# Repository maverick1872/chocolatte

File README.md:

# chocolatte
Custom split columnar (column staggered) keyboard heavily influenced on the crkbd, corne-ish zen, chocolad, and others

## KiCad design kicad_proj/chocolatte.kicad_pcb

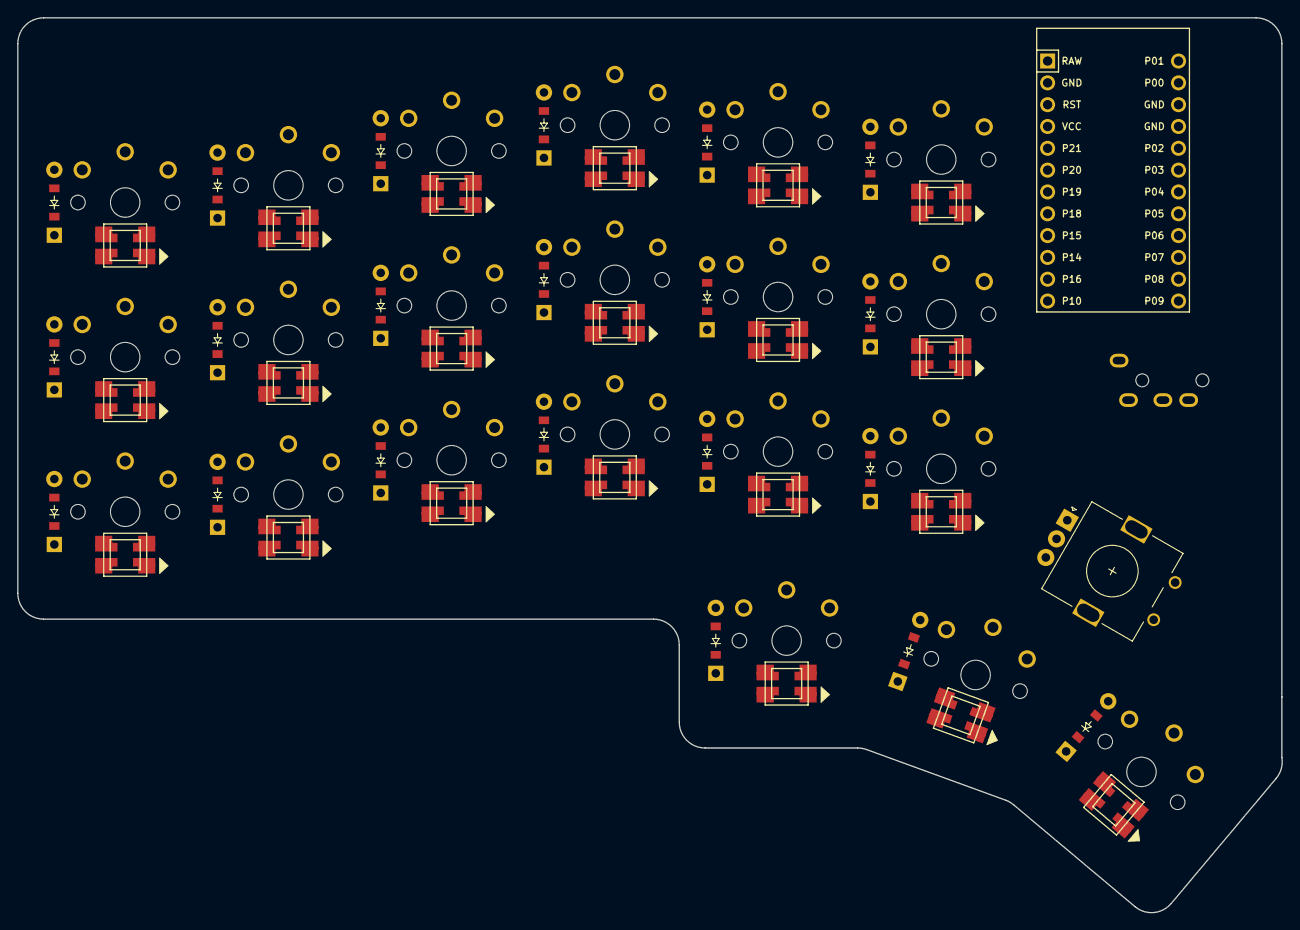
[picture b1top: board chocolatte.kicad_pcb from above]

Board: 2 copper layers, 147.2 x 104.2 mm, 65 parts (0 on the bottom side), 25 nets, no tracks yet.

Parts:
D1, D2, D3, D4, D5, D6, D7, D8, D9, D10, D11, D12, D13, D14, D15, D16, D17, D18, D19, D20, D21: ComboDiode
LED1, LED2, LED3, LED4, LED5, LED6, LED7, LED8, LED9, LED10, LED11, LED12, LED13, LED14, LED15, LED16, LED17, LED18, LED19, LED20, LED21: WS2812B
MCU1: ProMicro
ROT1: rotary_encoder
S1, S2, S3, S4, S5, S6, S7, S8, S9, S10, S11, S12, S13, S14, S15, S16, S17, S18, S19, S20, S21: PG1350

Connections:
GND: LED1.3, LED1.33, LED2.3, LED2.33, LED3.3, LED3.33, LED4.3, LED4.33, LED5.3, LED5.33, LED6.3, LED6.33, LED7.3, LED7.33, LED8.3, LED8.33, LED9.3, LED9.33, LED10.3, LED10.33, LED11.3, LED11.33, LED12.3, LED12.33, LED13.3, LED13.33, LED14.3, LED14.33, LED15.3, LED15.33, LED16.3, LED16.33, LED17.3, LED17.33, LED18.3, LED18.33, LED19.3, LED19.33, LED20.3, LED20.33, LED21.3, LED21.33, MCU1.2, MCU1.15, MCU1.16, ROT1.B, S1.2, S2.2, S3.2, S4.2, S5.2, S6.2, S7.2, S8.2, S9.2, S10.2, S11.2, S12.2, S13.2, S14.2, S15.2, S16.2, S17.2, S18.2, S19.2, S20.2, S21.2
VCC: LED1.1, LED1.11, LED2.1, LED2.11, LED3.1, LED3.11, LED4.1, LED4.11, LED5.1, LED5.11, LED6.1, LED6.11, LED7.1, LED7.11, LED8.1, LED8.11, LED9.1, LED9.11, LED10.1, LED10.11, LED11.1, LED11.11, LED12.1, LED12.11, LED13.1, LED13.11, LED14.1, LED14.11, LED15.1, LED15.11, LED16.1, LED16.11, LED17.1, LED17.11, LED18.1, LED18.11, LED19.1, LED19.11, LED20.1, LED20.11, LED21.1, LED21.11, MCU1.4
matrix_index_bottom: D13.1, D13.2, S13.1
matrix_index_home: D14.1, D14.2, MCU1.10, S14.1
matrix_index_top: D15.1, D15.2, MCU1.9, S15.1
matrix_inner_bottom: D16.1, D16.2, MCU1.11, S16.1
matrix_inner_home: D17.1, D17.2, S17.1
matrix_inner_top: D18.1, D18.2, MCU1.8, S18.1
matrix_middle_bottom: D10.1, D10.2, MCU1.12, S10.1
matrix_middle_home: D11.1, D11.2, S11.1
matrix_middle_top: D12.1, D12.2, S12.1
matrix_outer_bottom: D1.1, D1.2, MCU1.13, S1.1
matrix_outer_home: D2.1, D2.2, MCU1.17, S2.1
matrix_outer_top: D3.1, D3.2, MCU1.18, S3.1
matrix_pinky_bottom: D4.1, D4.2, MCU1.19, S4.1
matrix_pinky_home: D5.1, D5.2, MCU1.20, S5.1
matrix_pinky_top: D6.1, D6.2, MCU1.21, S6.1
matrix_ring_bottom: D7.1, D7.2, MCU1.22, S7.1
matrix_ring_home: D8.1, D8.2, MCU1.23, S8.1
matrix_ring_top: D9.1, D9.2, MCU1.24, S9.1
thumbfan_far_thumb: D21.1, D21.2, S21.1
thumbfan_home_thumb: D20.1, D20.2, S20.1
thumbfan_near_thumb: D19.1, D19.2, S19.1
undefined: ROT1.1, ROT1.2, ROT1.A, ROT1.C
unknown: D1.1, D1.2, D2.1, D2.2, D3.1, D3.2, D4.1, D4.2, D5.1, D5.2, D6.1, D6.2, D7.1, D7.2, D8.1, D8.2, D9.1, D9.2, D10.1, D10.2, D11.1, D11.2, D12.1, D12.2, D13.1, D13.2, D14.1, D14.2, D15.1, D15.2, D16.1, D16.2, D17.1, D17.2, D18.1, D18.2, D19.1, D19.2, D20.1, D20.2, D21.1, D21.2, LED1.2, LED1.4, LED1.22, LED1.44, LED2.2, LED2.4, LED2.22, LED2.44, LED3.2, LED3.4, LED3.22, LED3.44, LED4.2, LED4.4, LED4.22, LED4.44, LED5.2, LED5.4, LED5.22, LED5.44, LED6.2, LED6.4, LED6.22, LED6.44, LED7.2, LED7.4, LED7.22, LED7.44, LED8.2, LED8.4, LED8.22, LED8.44, LED9.2, LED9.4, LED9.22, LED9.44, LED10.2, LED10.4, LED10.22, LED10.44, LED11.2, LED11.4, LED11.22, LED11.44, LED12.2, LED12.4, LED12.22, LED12.44, LED13.2, LED13.4, LED13.22, LED13.44, LED14.2, LED14.4, LED14.22, LED14.44, LED15.2, LED15.4, LED15.22, LED15.44, LED16.2, LED16.4, LED16.22, LED16.44, LED17.2, LED17.4, LED17.22, LED17.44, LED18.2, LED18.4, LED18.22, LED18.44, LED19.2, LED19.4, LED19.22, LED19.44, LED20.2, LED20.4, LED20.22, LED20.44, LED21.2, LED21.4, LED21.22, LED21.44

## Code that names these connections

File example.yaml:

points:
  key:
    padding: cy
    footprints:
      choc:
        type: choc
        nets:
          from: =name
          to: GND
        params:
          keycaps: true
          reverse: true
      diode:
        type: diode
        params:
          tracks: true
        nets:
          from: =name
          to: unknown
        anchor:
          shift: [0, -5]

  zones:
    matrix:
      columns:
        outer:
        pinky:
          stagger: 2
        ring:
          stagger: 4
        middle:
          stagger: 3
        index:
          stagger: -2
        inner:
          stagger: -2
      rows:
        bottom:
        home:
        top:
    thumbfan:
      anchor:
        ref: matrix_inner_bottom
        shift: [-25, -20]
      columns:
        near:
        home:
          spread: cx+4
          stagger: -4
          rotate: -20
        far:
          spread: cx+4
          stagger: -4
          rotate: -20
      rows:
        thumb:

outlines:
  exports:
    keys:
      - type: keys
        side: left
        size: 18
    plate:
      - type: keys
        side: left
        size: 25
        corner: 4
    promicro_mounts:
      - type: rectangle
        anchor:
          - ref: matrix_middle_top
            shift: [0, (cy/2) + 4 ]
            rotate: 270
        size: [82,70]
        corner: 4
    merged:
      - type: outline # keys
        name: plate
      - type: outline
        name: promicro_mounts
        operation: add

    pcb_edgecut:
      - type: outline
        name: merged

cases:

# VIA footprints may be needed to jump between layers to avoid obstacles
# Use Blackpill controller to avoid having to leverage a diode matrix
# Potential for support MakerDiary m.2 bluetooth adapter https://wiki.makerdiary.com/nrf52840-m2
# USB-C Controller
# TRRS between halves
# Ability to make either halve master/slave pair
# Support for millmax hotswap sockets
# Support for Kailh hotswap sockets (default support in ergogen)
# Support for sk6812mini-e.js leds for easier soldering
# Support for Roller encoder, 1/side (EVQWGD001) (default support in ergogen)
# Support for Nice!View
pcbs:
  cholatte:
    outlines:
      pcb_outline_name:
        outline: pcb_edgecut
    footprints:
      - type: rotary
        anchor:
          - ref: matrix_inner_bottom
            shift: [20, -14]
            rotate: -32
        nets:
          to: undefined
          from: undefined
          A: undefined
          B: GND
          C: undefined

      - type: trrs
        anchor:
          - ref: matrix_inner_bottom
            shift: [34, 5]
            rotate: -90
        nets:
          A: GND
          B: GND
          C: D2
          D: VCC

      - type: oled # 4 pin oled; need to find 5pin footprint
        anchor:
          - ref: matrix_inner_top
            shift: [50, 0]
            rotate: 90
        nets:
          SDA: undefined,
          SCL: undefined,
          VCC: undefined,
          GND: undefined,

      - type: promicro
        anchor:
          - ref: matrix_inner_home
            shift: [25, 12]
            rotate: -90
        nets:
          P1: matrix_outer_bottom
          P2: matrix_outer_home
          P3: matrix_outer_top
          P4: matrix_pinky_bottom
          P5: matrix_pinky_home
          P6: matrix_pinky_top
          P7: matrix_ring_bottom
          P8: matrix_ring_home
          P9: matrix_ring_top
          P10: matrix_middle_bottom
          P11: matrix_middle_home
          P12: matrix_middle_top
          P13: matrix_index_bottom
          P14: matrix_index_home
          P15: matrix_index_top
          P16: matrix_inner_bottom
          P17: matrix_inner_home
          P18: matrix_inner_top
          P19: matrix_thumbfan_near
          P20: matrix_thumbfan_home
          P21: matrix_thumbfan_far

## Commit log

2022-11-09 init repo
2022-11-09 chorrect readme
2022-11-13 begin adding footprints to pcb and figuring out nets
2022-11-13 add gitkeep for gerbers dir
2022-11-13 add kicad proj
2022-11-13 update pcb name
2022-11-13 initial pcb edge cut design
2022-11-13 v0.1 maybe complete
2022-11-13 v0.1 kicad pcb
2022-11-13 custom sk6812mini-e footprint
2022-11-13 v0.1 ready for testing 3d printing and layout check
2022-11-13 fix file names
2022-11-13 add thorough example config
2022-11-13 add test stls to vcs
2022-11-15 minor updates
2023-01-03 add ergogen deps for local usage
2023-01-03 downgrade ergogen to v3 until v4 is actually ready for general use
2023-01-03 add additional padding/spread to main keys
2023-01-03 add ignored output dir
2023-01-06 make plate with proper key through hole for prototyping layout
2023-08-20 chore: makefile for easy generation and rename to indicate ergogen version
2023-08-20 chore: ensure version folders persist
2023-08-20 chore: start porting v3 to v4 ergogen
2023-08-21 chore: continue updating v4 declaration
